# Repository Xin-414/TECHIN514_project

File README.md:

# Cat Feeding Activity Indicator

A connected device system that monitors how frequently a cat visits its food bowl and provides a physical gauge display to indicate when it may be time to refill the food.

This project was developed for TECHIN 514.

---

## Overview

Cat owners often do not know when their cat’s food bowl needs refilling. Cats may repeatedly visit an empty bowl without the owner noticing.

This project addresses this problem by monitoring motion near the food bowl and visualizing feeding-related activity through a physical gauge display.

*Figure: Design sketches.*

The system consists of two connected devices:  
• **Sensor Device** – detects cat motion near the food bowl  
• **Display Device** – visualizes feeding activity using a gauge needle and LED indicator

When the cat frequently approaches the bowl, the system indicates that the bowl may need refilling.

---

## System Architecture

The system includes two ESP32-based devices communicating wirelessly using **ESP-NOW**.

Workflow:

PIR Motion Detection  
→ Event Debounce Filtering  
→ Activity Counter  
→ Wireless Transmission (ESP-NOW)  
→ Gauge Needle Rotation  
→ LED Alert

---

## Hardware Components

### Sensor Device

Placed near the cat’s food bowl.

Components:
- PIR Motion Sensor (HC-SR501)
- Seeed XIAO ESP32-S3
- Capacitors
- Resistor
- USB-C power

Function:

Detects motion events near the food bowl and sends activity counts wirelessly to the display device.

---

### Display Device

Placed in a visible location for the owner.

Components:  
- Seeed XIAO ESP32-C3
- X27.168 bipolar stepper motor gauge
- LED indicator
- Push button switch
- 330Ω resistor
- 3.7V 1000mAh LiPo battery

Function:

Receives activity data and maps it to a gauge needle position that indicates feeding activity level.

---
## Schematics & PCB layout

The system includes custom circuit schematics and PCB layout for both sensing and display devices.

*Figure: Schematics*

*Figure: PCB layout of sensor device.*

## Signal Processing

Motion signals from the PIR sensor are filtered using a debounce time window to avoid multiple triggers from a single visit.

Processing pipeline:  

During testing, the system detected **18 out of 20 simulated bowl visits**, resulting in an estimated **90% detection accuracy**. :contentReference[oaicite:0]{index=0}

---

## Demo

Demo video: https://drive.google.com/file/d/1uZkeXHpC4BiWEvxUYPUGvsP9ljvaZRCp/view

---

## Battery Considerations

The display device is powered by a **3.7V 1000mAh LiPo battery**.

Battery life estimation was calculated based on:

- ESP32 power consumption  
- LED activity  
- Stepper motor usage  
- Communication duty cycle

Power analysis was used to determine expected operating duration and ensure reliable device operation.

### Spreadsheet
Google Sheets (view-only):  
https://docs.google.com/spreadsheets/d/10LHwdyrkDoTDUunTCcTbiJU-1OUqTOgCYg1e28etRiU/edit?usp=sharing

### Screenshots
- Display Device Power Model  
  
- Sensor Device Power Model  

---

## Budget Summary

| Component | Quantity | Cost |
|-----------|----------|------|
| ESP32-C3 | 2 | $21.98 |
| LiPo Battery | 2 | $15.90 |
| PIR Motion Sensor | 1 | — |
| X27 Stepper Motor | 1 | — |
| Other components (resistors, LEDs, capacitors) | — | — |

Total project cost is approximately **$40–50** depending on sourcing and additional components.

---

## Future Work

Possible future improvements include:

**Behavior-aware detection**  
Improve sensing reliability and reduce false triggers caused by nearby motion.

**Machine learning analysis**  
Use motion pattern analysis to distinguish feeding behavior from other movement near the bowl.

**Multi-device ecosystem**  
Support multiple food bowls or multiple pets by connecting additional sensor devices.

**Data logging and mobile interface**  
Store feeding activity data and visualize it through a mobile application or dashboard.

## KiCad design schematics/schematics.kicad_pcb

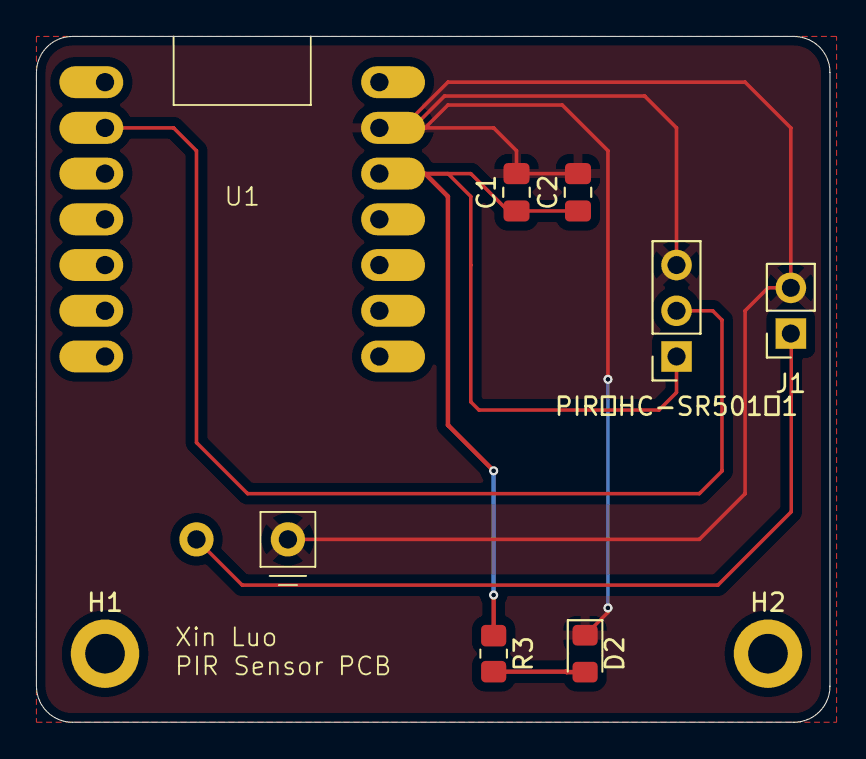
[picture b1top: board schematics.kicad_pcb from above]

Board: 2 copper layers, 44.1 x 38.1 mm, 9 parts (0 on the bottom side), 5 nets.

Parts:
C1: 0.1uF; C_0805_2012Metric_Pad1.18x1.45mm_HandSolder
C2: 10uF; C_0805_2012Metric_Pad1.18x1.45mm_HandSolder
D2: LED; LED_0805_2012Metric_Pad1.15x1.40mm_HandSolder
H1, H2: MountingHole_Pad; MountingHole_2.2mm_M2_DIN965_Pad
J1: Conn_01x02; PinSocket_1x02_P2.54mm_Vertical
PIR（HC-SR501）1: Conn_01x03_Pin; PinSocket_1x03_P2.54mm_Vertical
R3: 500Ω; R_0805_2012Metric_Pad1.20x1.40mm_HandSolder
U1: XIAO_ESP32

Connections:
/3V3: C1.1, C2.1, PIR（HC-SR501）1.1, R3.1, U1.12 (3V3)
/D1: PIR（HC-SR501）1.2, U1.2 (GPIO2_A1_D1)
GND: C1.2, C2.2, D2.1 (K), J1.2 (-BATT), PIR（HC-SR501）1.3, U1.13 (GND), U1.16 (-BATT)
unnamed: D2.2 (A), R3.2
unnamed: J1.1 (+BATT), U1.15 (+BATT)

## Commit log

2026-01-20 readme
2026-01-20 Add README structure for system architecture
2026-01-20 Add sensing device sketch
2026-01-20 add images
2026-01-20 Display Device
2026-01-20 System Architecture
2026-01-20 Add ESP32-C3 datasheets
2026-01-20 Add PIR sensor datasheet and 28BYJ-48 stepper motor datasheet
2026-01-20 add ULN2003 Stepper Motor Driver Datasheet
2026-01-20 add Generic LED Datasheet
2026-01-20 Tactile Push Button Datasheet
2026-01-20 add LiPo Battery Datasheet (3.7V)
2026-01-20 adjust layout
2026-01-26 Add KiCad schematics for final project
2026-01-26 add BOM
2026-02-03 update schematics
2026-02-09 add Power & Battery Analysis
2026-02-14 adjust schematics
2026-02-23 adjust pcb design
2026-02-28 display device code
2026-03-02 update datasheets
2026-03-16 readme update
2026-03-16 battery life update
